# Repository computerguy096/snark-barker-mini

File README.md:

# The Snark Barker Mini - a miniaturized SB 1.0 Clone

The Snark Barker Mini is a function compatible clone of the original [Snark Barker](https://github.com/schlae/snark-barker), made by schlae. It implements all the features of the original Sound Blaster:

- OPL2 FM synth
- digital sound playback and recording
- gameport with MIDI IN/OUT
- SAA1099 (Creative Music System) synth 

The only major difference is the lack of a volume potentiometer. Due to the card's size and parts availability contraints, the volume is pre-set at max output, but this should not be a problem for speaker systems which have adjustable volume.

## Bill Of Materials
An interactive HTML BOM is provided in `/kicad/bom` for easy parts installation. Most passives do not have silkscreen labels so this will be needed. Additionally, a CSV BOM is provided as well.

## The Firmware
This card uses an Atmel 89LP51 as a modern day replacement for the original 80C51 microcontroller Creative used to implement the DSP chip. There is a programming header provided for the DSP chip, which can be flashed with [this HEX file](firmware/sb.hex) using the tool of your choice. 

The DSP PWR jumper needs to be installed for normal operation, and removed when programming the DSP (it connects the DSP to VCC).

## Testing and Diagnostics
The card can be tested using schlae's [SBDIAG](utility/SBDIAG.EXE)

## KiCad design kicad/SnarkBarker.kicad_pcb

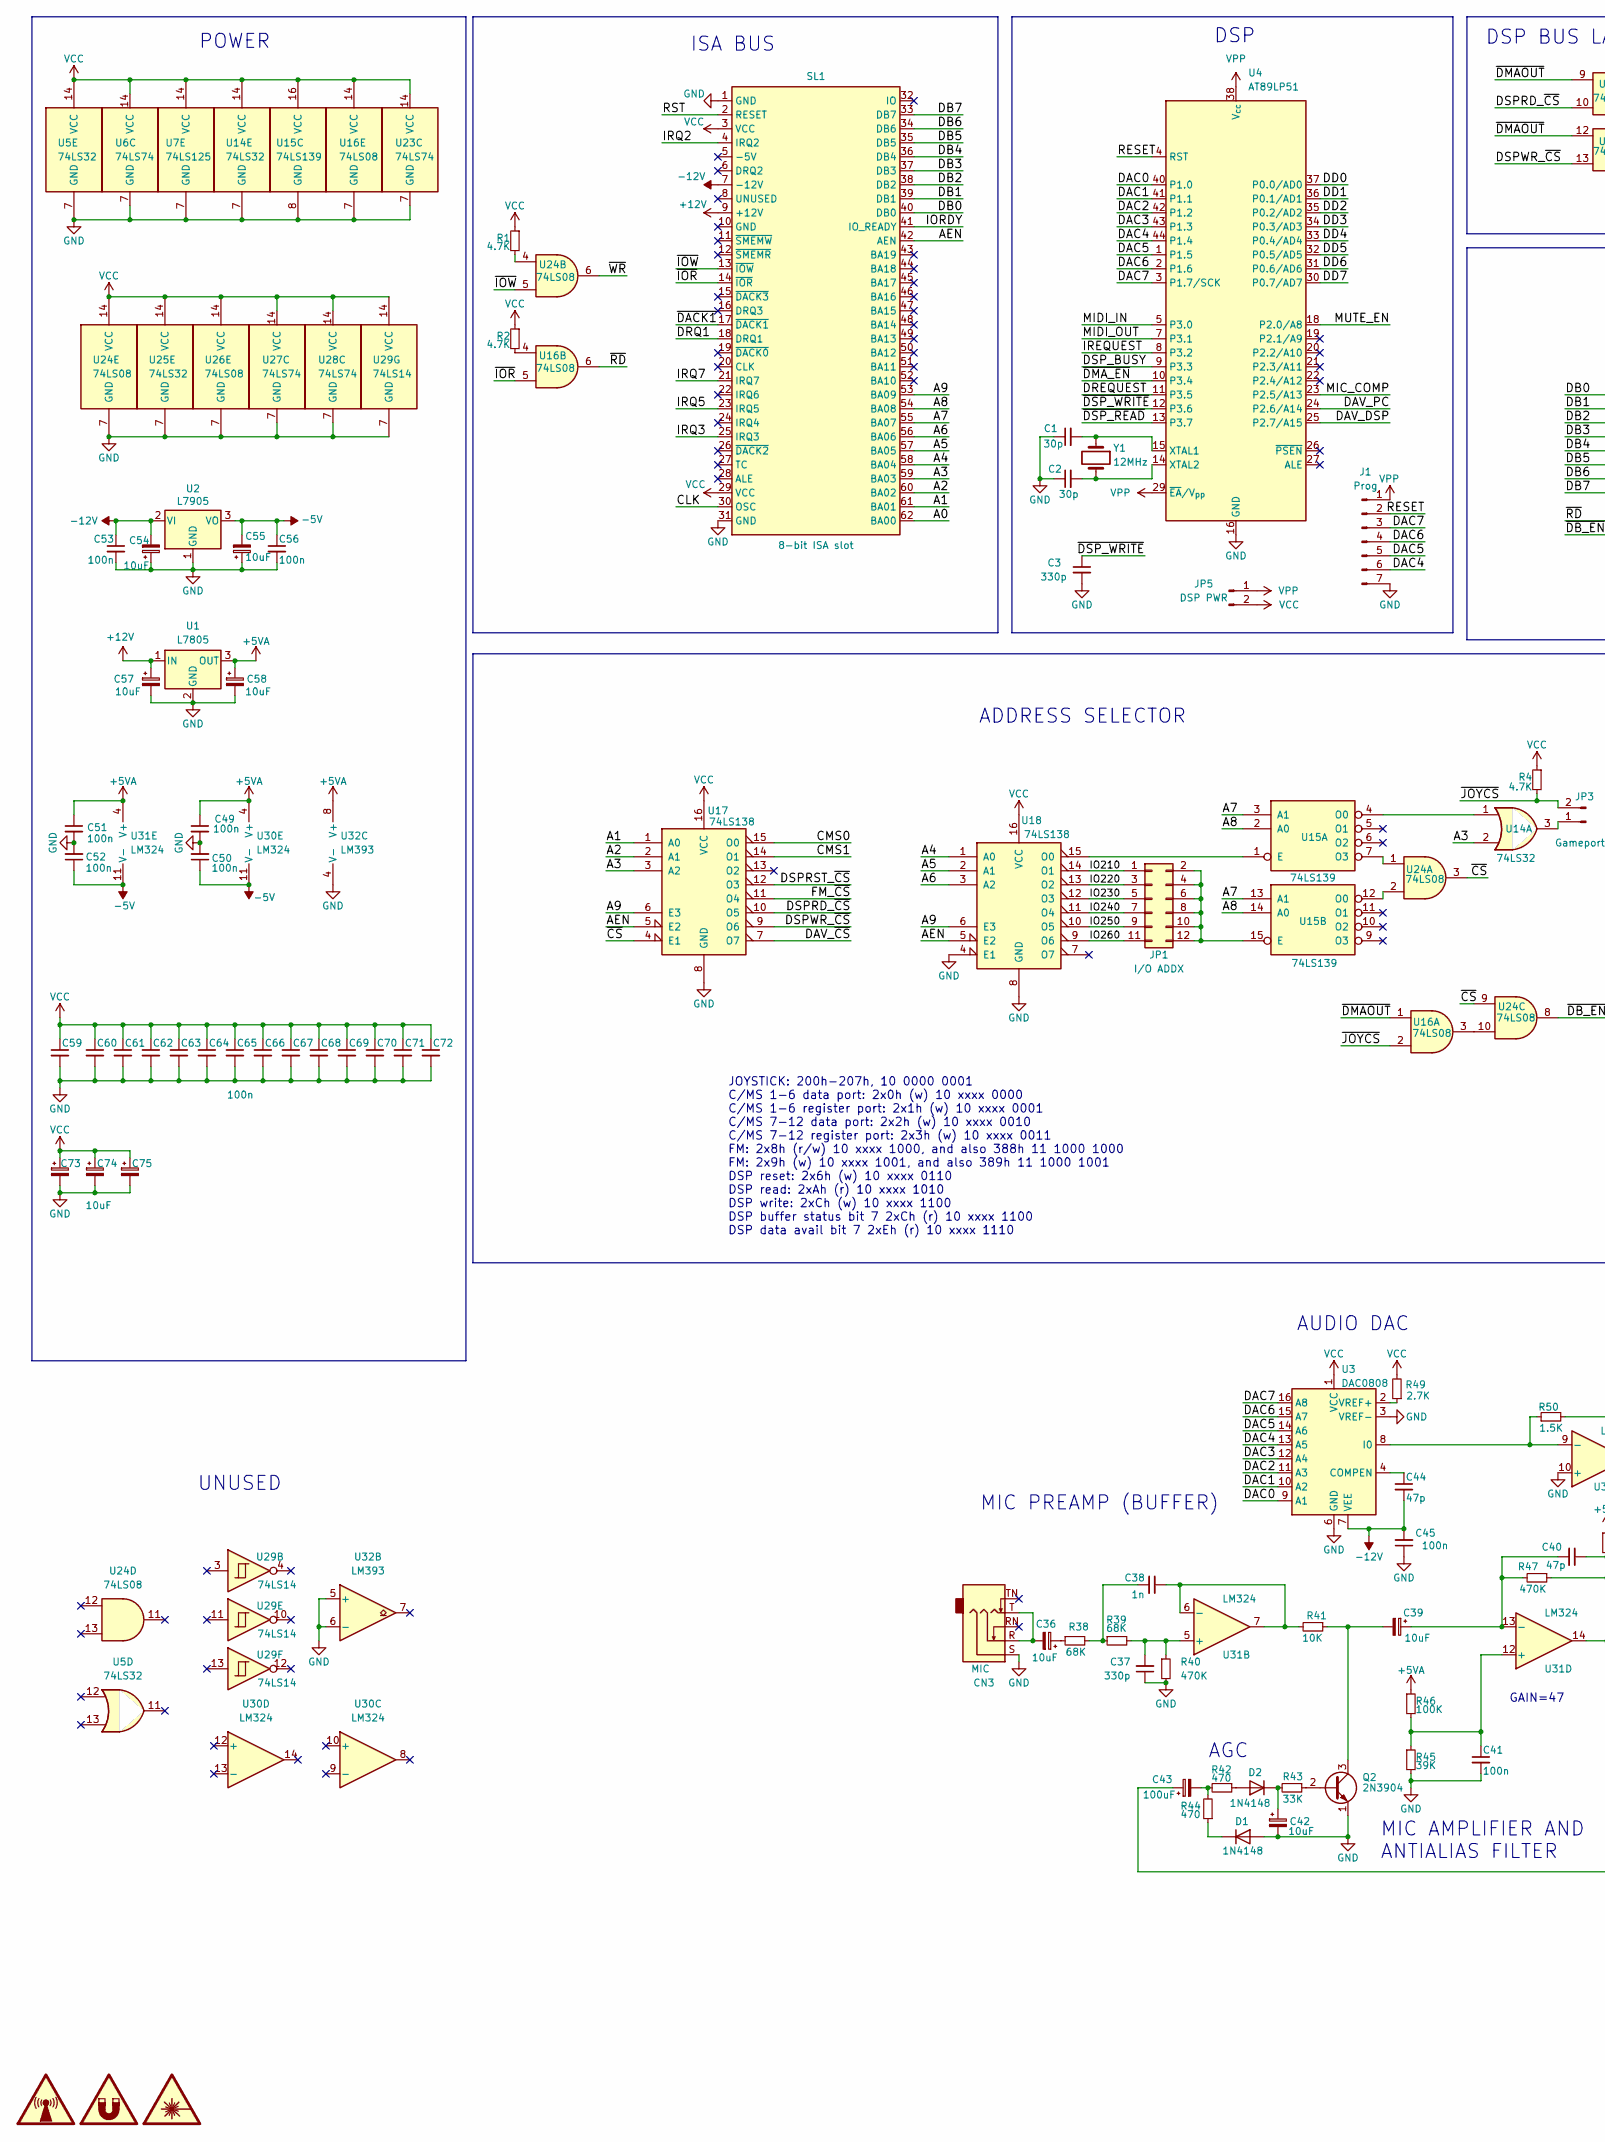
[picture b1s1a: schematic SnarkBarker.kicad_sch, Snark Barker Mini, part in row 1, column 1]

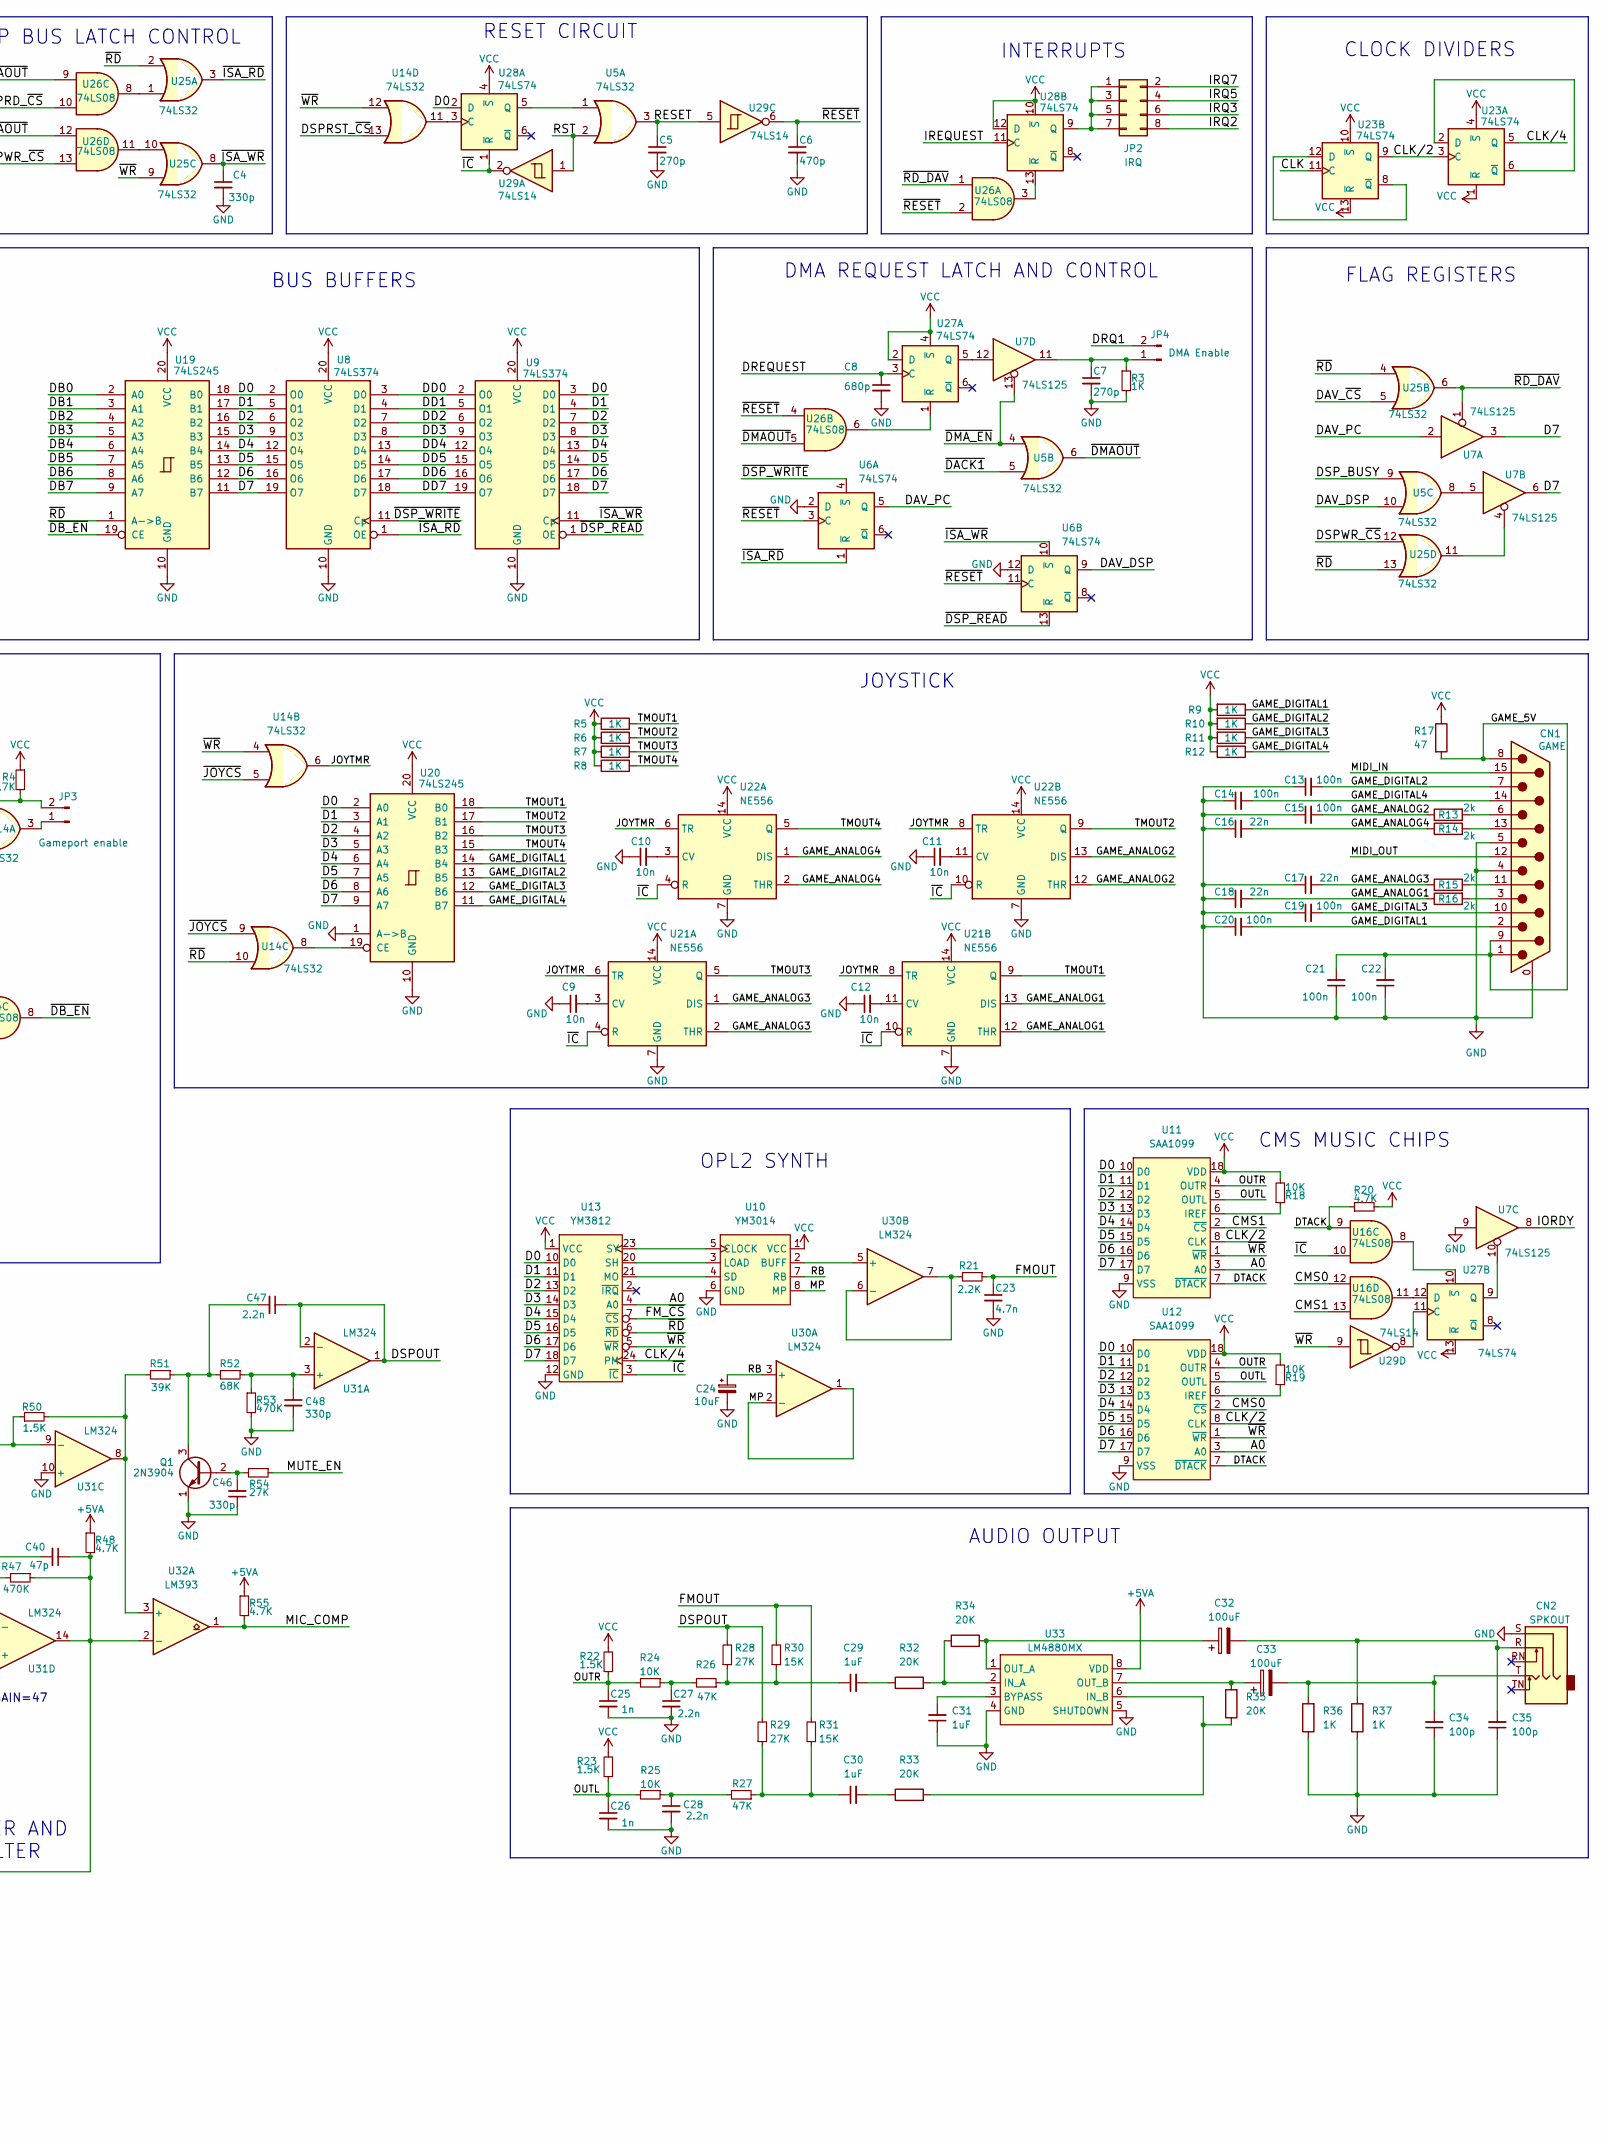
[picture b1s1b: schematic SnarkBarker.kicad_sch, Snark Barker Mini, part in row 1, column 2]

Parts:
C1, C2: 30p; C_0805_2012Metric; Mouser 810-FG28C0G1H270JNT6
C3, C4, C37, C46, C48: 330p; C_0805_2012Metric; Mouser 810-FG28C0G1H331JNT6
C5, C7: 270p; C_0805_2012Metric; Mouser 810-FG28C0G1H271JNT0
C6: 470p; C_0805_2012Metric; Mouser 810-FG28C0G1H471JNT6
C8: 680p; C_0805_2012Metric; Mouser 810-FG28C0G1H681JNT6
C9, C10, C11, C12: 10n; C_0805_2012Metric; Mouser 810-FG28X7R1H103KNT0
C13, C14, C15, C19, C20, C21, C22: 100n; C_0805_2012Metric
C16, C17, C18: 22n; C_0805_2012Metric
C23: 4.7n; C_0805_2012Metric; Mouser 810-FG28C0G1H472JNT6
C24, C36, C39, C42, C54, C55, C57, C58, C73, C74, C75: 10uF; C_1210_3225Metric; Mouser 667-ECA-1CM100I
C25, C26, C38: 1n; C_0805_2012Metric; Mouser 810-FG28X7R1H102KNT6
C27, C28, C47: 2.2n; C_0805_2012Metric; Mouser 810-FG28X7R1H222KNT6
C29, C30, C31: 1uF; C_0805_2012Metric
C32, C33: 100uF; CP_Elec_6.3x5.2
C34, C35: 100p; C_0805_2012Metric
C40, C44: 47p; C_0805_2012Metric; Mouser 810-FG28C0G1H470JNT6
C41, C45, C49, C50, C51, C52, C53, C56, C59, C60, C61, C62, C63, C64, C65, C66, C67, C68, C69, C70, C71, C72: 100n; C_0805_2012Metric; Mouser 581-SA105E104M
C43: 100uF; CP_Elec_6.3x5.2; Mouser 667-ECA-1CM101I
CN1: GAME; DSUB-15_Pins_Horizontal_P2.77x2.84mm_EdgePinOffset7.70mm_Ho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
CN2: SPKOUT; TRS jack
CN3: MIC; TRS jack
D1, D2: 1N4148; D_0805_2012Metric; Mouser 512-1N4148
J1: Prog; PinHeader_1x07_P2.54mm_Vertical
JP1: I/O ADDX; PinHeader_2x06_P2.54mm_Vertical
JP2: IRQ; PinHeader_2x04_P2.54mm_Vertical
JP3: Gameport enable; PinHeader_1x02_P2.54mm_Vertical
JP4: DMA Enable; PinHeader_1x02_P2.54mm_Vertical
JP5: DSP PWR; PinHeader_1x02_P2.54mm_Vertical
Q1, Q2: 2N3904; SOT-23; Mouser 833-2N3904-AP
R1, R2, R4, R20, R48, R55: 4.7K; R_0805_2012Metric; Mouser 603-CFR-25JB-52-4K7
R3: 1K; R_0805_2012Metric; Mouser 603-CFR-25JR-521K
R5, R6, R7, R8, R9, R10, R11, R12, R36, R37: 1K; R_0805_2012Metric
R13, R14, R15, R16: 2k; R_0805_2012Metric
R17: 47; R_0805_2012Metric
R18, R19, R24, R25, R41: 10K; R_0805_2012Metric; Mouser 603-CFR-25JB-52-10K
R21: 2.2K; R_0805_2012Metric; Mouser 603-CFR-25JB-52-2K2
R22, R23: 1.5K; R_0805_2012Metric; Mouser 603-CFR-25JB-52-1K5
R26, R27: 47K; R_0805_2012Metric; Mouser 603-CFR-25JB-52-47K
R28, R29, R54: 27K; R_0805_2012Metric; Mouser 603-CFR-25JB-52-27K
R30, R31: 15K; R_0805_2012Metric; Mouser 603-CFR-25JB-52-15K
R32, R33, R34, R35: 20K; R_0805_2012Metric
R38, R39, R52: 68K; R_0805_2012Metric; Mouser 603-CFR-25JB-52-68K
R40, R47, R53: 470K; R_0805_2012Metric; Mouser 603-CFR-25JR-52470K
R42, R44: 470; R_0805_2012Metric; Mouser 603-CFR-25JB-52-470R
R43: 33K; R_0805_2012Metric; Mouser 603-CFR-25JB-52-33K
R45: 39K; R_0805_2012Metric; Mouser 603-MFR-25FBF52-39K
R46: 100K; R_0805_2012Metric; Mouser 603-MFR-25FBF52-100K
R49: 2.7K; R_0805_2012Metric; Mouser 603-MFR-25FBF52-2K7
R50: 1.5K; R_0805_2012Metric; Mouser 603-MFR-25FBF52-1K5
R51: 39K; R_0805_2012Metric; Mouser 603-CFR-25JB-52-39K
SL1: 8-bit ISA slot; ISA card edge
U1: L7805; TO-220-3_Horizontal_TabDown
U2: L7905; TO-220-3_Horizontal_TabDown
U3: DAC0808; SOIC-16_3.9x9.9mm_P1.27mm
U4: AT89LP51; TQFP-44_10x10mm_P0.8mm
U5, U14: 74LS32; SOIC-14_3.9x8.7mm_P1.27mm
U6: 74LS74; SOIC-14_3.9x8.7mm_P1.27mm
U7: 74LS125; SOIC-14_3.9x8.7mm_P1.27mm; Mouser 595-SN74LS125AN
U8, U9: 74LS374; SOIC-20W_7.5x12.8mm_P1.27mm; Mouser 595-SN74LS374N
U10: YM3014; DIP-8_W7.62mm
U11, U12: SAA1099; DIP-18_W7.62mm
U13: YM3812; DIP-24_W15.24mm
U15: 74LS139; SOIC-16_3.9x9.9mm_P1.27mm; Mouser 595-SN74LS139AN
U16, U24, U26: 74LS08; SOIC-14_3.9x8.7mm_P1.27mm
U17, U18: 74LS138; SOIC-16_3.9x9.9mm_P1.27mm; Mouser 595-SN74LS138NE4
U19, U20: 74LS245; SOIC-20W_7.5x12.8mm_P1.27mm; Mouser 595-SN74LS245N
U21, U22: NE556; SOIC-14_3.9x8.7mm_P1.27mm
U23, U27, U28: 74LS74; SOIC-14_3.9x8.7mm_P1.27mm; Mouser 595-SN74LS74AN
U25: 74LS32; SOIC-14_3.9x8.7mm_P1.27mm; Mouser 595-SN74LS32N
U29: 74LS14; SOIC-14_3.9x8.7mm_P1.27mm; Mouser 595-SN74LS14N
U30: LM324; SOIC-14_3.9x8.7mm_P1.27mm
U31: LM324; SOIC-14_3.9x8.7mm_P1.27mm; Mouser 512-LM324AN
U32: LM393; SOIC-8_3.9x4.9mm_P1.27mm
U33: LM4880MX; SO-8_3.9x4.9mm_P1.27mm
Y1: 12MHz; Crystal_HC49-U_Vertical

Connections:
+5VA: C49.1, C51.1, C58.1, R46.1, R48.1, R55.1, U1.3 (OUT), U30.4 (V+), U31.4 (V+), U32.8 (V+), U33.8 (VDD)
+12V: C57.1, SL1.9 (+12V), U1.1 (IN)
-5V: C50.1, C52.1, C55.2, C56.1, U2.3 (VO), U30.11 (V-), U31.11 (V-)
-12V: C44.2, C45.2, C53.1, C54.2, SL1.7 (-12V), U2.2 (VI), U3.7 (VEE)
/A0: SL1.62 (BA00), U11.3 (A0), U12.3 (A0), U13.4 (A0)
/A1: SL1.61 (BA01), U17.1 (A0)
/A2: SL1.60 (BA02), U17.2 (A1)
/A3: SL1.59 (BA03), U14.2, U17.3 (A2)
/A4: SL1.58 (BA04), U18.1 (A0)
/A5: SL1.57 (BA05), U18.2 (A1)
/A6: SL1.56 (BA06), U18.3 (A2)
/A7: SL1.55 (BA07), U15.3 (A1), U15.13 (A1)
/A8: SL1.54 (BA08), U15.2 (A0), U15.14 (A0)
/A9: SL1.53 (BA09), U17.6 (E3), U18.6 (E3)
/AEN: SL1.42 (AEN), U17.5 (E2), U18.5 (E2)
/CLK: SL1.30 (OSC), U23.11 (C)
/CLK/2: U11.8 (CLK), U12.8 (CLK), U23.3 (C), U23.9 (Q)
/CLK/4: U13.24 (PM), U23.5 (Q)
/CMS0: U12.2 (~CS), U16.12, U17.15 (O0)
/CMS1: U11.2 (~CS), U16.13, U17.14 (O1)
/D0: U8.2 (O0), U9.3 (D0), U11.10 (D0), U12.10 (D0), U13.10 (D0), U19.18 (B0), U20.2 (A0), U28.2 (D)
/D1: U8.5 (O1), U9.4 (D1), U11.11 (D1), U12.11 (D1), U13.11 (D1), U19.17 (B1), U20.3 (A1)
/D2: U8.6 (O2), U9.7 (D2), U11.12 (D2), U12.12 (D2), U13.13 (D2), U19.16 (B2), U20.4 (A2)
/D3: U8.9 (O3), U9.8 (D3), U11.13 (D3), U12.13 (D3), U13.14 (D3), U19.15 (B3), U20.5 (A3)
/D4: U8.12 (O4), U9.13 (D4), U11.14 (D4), U12.14 (D4), U13.15 (D4), U19.14 (B4), U20.6 (A4)
/D5: U8.15 (O5), U9.14 (D5), U11.15 (D5), U12.15 (D5), U13.16 (D5), U19.13 (B5), U20.7 (A5)
/D6: U8.16 (O6), U9.17 (D6), U11.16 (D6), U12.16 (D6), U13.17 (D6), U19.12 (B6), U20.8 (A6)
/D7: U7.3, U7.6, U8.19 (O7), U9.18 (D7), U11.17 (D7), U12.17 (D7), U13.18 (D7), U19.11 (B7), U20.9 (A7)
/DAC0: U3.9 (A1), U4.40 (P1.0)
/DAC1: U3.10 (A2), U4.41 (P1.1)
/DAC2: U3.11 (A3), U4.42 (P1.2)
/DAC3: U3.12 (A4), U4.43 (P1.3)
/DAC4: J1.6, U3.13 (A5), U4.44 (P1.4)
/DAC5: J1.5, U3.14 (A6), U4.1 (P1.5)
/DAC6: J1.4, U3.15 (A7), U4.2 (P1.6)
/DAC7: J1.3, U3.16 (A8), U4.3 (P1.7/SCK)
/DAV_DSP: U4.25 (P2.7/A15), U5.10, U6.9 (Q)
/DAV_PC: U4.24 (P2.6/A14), U6.5 (Q), U7.2
/DAV_~CS: U17.7 (O7), U25.5
/DB0: SL1.40 (DB0), U19.2 (A0)
/DB1: SL1.39 (DB1), U19.3 (A1)
/DB2: SL1.38 (DB2), U19.4 (A2)
/DB3: SL1.37 (DB3), U19.5 (A3)
/DB4: SL1.36 (DB4), U19.6 (A4)
/DB5: SL1.35 (DB5), U19.7 (A5)
/DB6: SL1.34 (DB6), U19.8 (A6)
/DB7: SL1.33 (DB7), U19.9 (A7)
/DD0: U4.37 (P0.0/AD0), U8.3 (D0), U9.2 (O0)
/DD1: U4.36 (P0.1/AD1), U8.4 (D1), U9.5 (O1)
/DD2: U4.35 (P0.2/AD2), U8.7 (D2), U9.6 (O2)
/DD3: U4.34 (P0.3/AD3), U8.8 (D3), U9.9 (O3)
/DD4: U4.33 (P0.4/AD4), U8.13 (D4), U9.12 (O4)
/DD5: U4.32 (P0.5/AD5), U8.14 (D5), U9.15 (O5)
/DD6: U4.31 (P0.6/AD6), U8.17 (D6), U9.16 (O6)
/DD7: U4.30 (P0.7/AD7), U8.18 (D7), U9.19 (O7)
/DREQUEST: C8.1, U4.11 (P3.5), U27.3 (C)
/DRQ1: JP4.2, SL1.18 (DRQ1)
/DSPOUT: C47.1, R28.2, R29.2, U31.1, U31.2 (-)
/DSPRD_~CS: U17.10 (O5), U26.10
/DSPRST_~CS: U14.13, U17.12 (O3)
/DSPWR_~CS: U17.9 (O6), U25.12, U26.13
/DSP_BUSY: U4.9 (P3.3), U5.9
/DTACK: R20.1, U11.7 (~DTACK), U12.7 (~DTACK), U16.9
/FMOUT: C23.1, R21.1, R30.2, R31.2
/FM_~CS: U13.7 (~CS), U17.11 (O4)
/GAME_5V: C21.2, C22.2, CN1.1, CN1.8, CN1.9, R17.2
/GAME_ANALOG1: C18.2, R16.1, U21.12 (THR), U21.13 (DIS)
/GAME_ANALOG2: C15.2, R13.1, U22.12 (THR), U22.13 (DIS)
/GAME_ANALOG3: C17.2, R15.1, U21.1 (DIS), U21.2 (THR)
/GAME_ANALOG4: C16.2, R14.1, U22.1 (DIS), U22.2 (THR)
/GAME_DIGITAL1: C20.2, CN1.2, R9.1, U20.14 (B4)
/GAME_DIGITAL2: C13.2, CN1.7, R10.1, U20.13 (B5)
/GAME_DIGITAL3: C19.2, CN1.10, R11.1, U20.12 (B6)
/GAME_DIGITAL4: C14.2, CN1.14, R12.1, U20.11 (B7)
/IO210: JP1.1, U18.14 (O1)
/IO220: JP1.3, U18.13 (O2)
/IO230: JP1.5, U18.12 (O3)
/IO240: JP1.7, U18.11 (O4)
/IO250: JP1.9, U18.10 (O5)
/IO260: JP1.11, U18.9 (O6)
/IORDY: SL1.41 (IO_READY), U7.8
/IREQUEST: U4.8 (P3.2), U28.11 (C)
/IRQ2: JP2.8, SL1.4 (IRQ2)
/IRQ3: JP2.6, SL1.25 (IRQ3)
/IRQ5: JP2.4, SL1.23 (IRQ5)
/IRQ7: JP2.2, SL1.21 (IRQ7)
/JOYTMR: U14.6, U21.6 (TR), U21.8 (TR), U22.6 (TR), U22.8 (TR)
/MIC_COMP: R55.2, U4.23 (P2.5/A13), U32.1
/MIDI_IN: CN1.15, U4.5 (P3.0)
/MIDI_OUT: CN1.12, U4.7 (P3.1)
/MP: U10.8 (MP), U30.1, U30.2 (-)
/MUTE_EN: R54.1, U4.18 (P2.0/A8)
/OUTL: C26.1, R23.1, R25.2, U11.5 (OUTL), U12.5 (OUTL)
/OUTR: C25.1, R22.1, R24.2, U11.4 (OUTR), U12.4 (OUTR)
/RB: C24.1, U10.7 (RB), U30.3 (+)
/RESET: C5.1, J1.2, U4.4 (RST), U5.3, U29.5
/RST: SL1.2 (RESET), U5.2, U29.1
/TMOUT1: R5.2, U20.18 (B0), U21.9 (Q)
/TMOUT2: R6.2, U20.17 (B1), U22.9 (Q)
/TMOUT3: R7.2, U20.16 (B2), U21.5 (Q)
/TMOUT4: R8.2, U20.15 (B3), U22.5 (Q)
/~CS: U17.4 (E1), U24.3, U24.9
/~DACK1: SL1.17 (~DACK1), U5.5
/~DB_EN: U19.19 (CE), U24.8
/~DMAOUT: U5.6, U16.1, U26.5, U26.9, U26.12
/~DMA_EN: U4.10 (P3.4), U5.4, U7.13
/~DSP_READ: U4.13 (P3.7), U6.13 (~R), U9.1 (OE)
/~DSP_WRITE: C3.1, U4.12 (P3.6), U6.4 (~S), U8.11 (Cp)
/~IC: U13.3 (~IC), U16.10, U21.4 (R), U21.10 (R), U22.4 (R), U22.10 (R), U28.1 (~R), U29.2
/~IOR: SL1.14 (~IOR), U16.5
/~IOW: SL1.13 (~IOW), U24.5
/~ISA_RD: U6.1 (~R), U8.1 (OE), U25.3
/~ISA_WR: C4.1, U6.10 (~S), U9.11 (Cp), U25.8
/~JOYCS: JP3.2, R4.2, U14.5, U14.9, U16.2
/~RD_DAV: U7.1, U25.6, U26.1
/~RD: U13.6 (~RD), U14.10, U16.6, U19.1 (A->B), U25.2, U25.4, U25.13
/~RESET: C6.1, U6.3 (C), U6.11 (C), U26.2, U26.4, U29.6
/~WR: U11.1 (~WR), U12.1 (~WR), U13.5 (~WR), U14.4, U14.12, U24.6, U25.9, U29.9
GND: C1.1, C2.1, C3.2, C4.2, C5.2, C6.2, C7.2, C8.2, C9.1, C10.1, C11.1, C12.1, C13.1, C14.1, C15.1, C16.1, C17.1, C18.1, C19.1, C20.1, C21.1, C22.1, C23.2, C24.2, C25.2, C26.2, C27.2, C28.2, C31.1, C34.1, C35.1, C37.1, C41.2, C42.2, C45.1, C46.1, C48.2, C49.2, C50.2, C51.2, C52.2, C53.2, C54.1, C55.1, C56.2, C57.2, C58.2, C59.2, C60.2, C61.2, C62.2, C63.2, C64.2, C65.2, C66.2, C67.2, C68.2, C69.2, C70.2, C71.2, C72.2, C73.2, C74.2, C75.2, CN1.0 (PAD), CN1.4, CN1.5, CN2.S, CN3.S, D1.2 (A), J1.7, Q1.1 (E), Q2.1 (E), R3.2, R36.1, R37.1, R40.2, R45.2, R53.2, SL1.1 (GND), SL1.31 (GND), U1.2 (GND), U2.1 (GND), U3.3 (VREF-), U3.6 (GND), U4.16 (GND), U4.17 (GND), U5.7 (GND), U6.2 (D), U6.7 (GND), U6.12 (D), U7.7 (GND), U7.9, U8.10 (GND), U9.10 (GND), U10.6 (GND), U11.9 (VSS), U12.9 (VSS), U13.12 (GND), U14.7 (GND), U15.8 (GND), U16.7 (GND), U17.8 (GND), U18.4 (E1), U18.8 (GND), U19.10 (GND), U20.1 (A->B), U20.10 (GND), U21.7 (GND), U22.7 (GND), U23.7 (GND), U24.7 (GND), U25.7 (GND), U26.7 (GND), U27.7 (GND), U28.7 (GND), U29.7 (GND), U31.10 (+), U32.4 (V-), U32.5 (+), U32.6 (-), U33.4 (GND), U33.5 (SHUTDOWN)
unnamed: C27.1, R24.1, R26.2
unnamed: C28.1, R25.1, R27.2
unnamed: C29.1, R26.1, R28.1, R30.1
unnamed: C29.2, R32.1
unnamed: C30.1, R27.1, R29.1, R31.1
unnamed: C30.2, R33.1
unnamed: C32.2, C35.2, CN2.R, R37.2
unnamed: C33.2, C34.2, CN2.T, R36.2
unnamed: C36.1, R38.1
unnamed: C36.2, CN3.R, CN3.T
unnamed: C38.2, R38.2, R39.1
unnamed: C43.2, R42.2, R44.2
unnamed: CN1.13, R14.2
unnamed: CN1.11 (P111), R15.2
unnamed: CN1.3, R16.2
unnamed: CN1.6, R13.2
unnamed: D1.1 (K), R44.1
unnamed: D2.2 (A), R42.1
unnamed: C42.1, D2.1 (K), R43.2
unnamed: JP1.2, JP1.4, JP1.6, JP1.8, JP1.10, JP1.12, U15.15 (E)
unnamed: JP2.1, JP2.3, JP2.5, JP2.7, U28.9 (Q)
unnamed: JP3.1, U14.3
unnamed: C7.1, JP4.1, R3.1, U7.11
unnamed: C46.2, Q1.2 (B), R54.2
unnamed: C47.2, Q1.3 (C), R51.1, R52.2
unnamed: Q2.2 (B), R43.1
unnamed: C39.2, Q2.3 (C), R41.1
unnamed: R1.2, U24.4
unnamed: R2.2, U16.4
unnamed: C44.1, U3.4 (COMPEN)
unnamed: R50.1, U3.8 (I0), U31.9 (-)
unnamed: R49.1, U3.2 (VREF+)
unnamed: C1.2, U4.15 (XTAL1), Y1.1
unnamed: C2.2, U4.14 (XTAL2), Y1.2
unnamed: U5.8, U7.5
unnamed: U10.2 (BUFF), U30.5 (+)
unnamed: U10.5 (CLOCK), U13.23 (SY)
unnamed: U10.3 (LOAD), U13.20 (SH)
unnamed: U10.4 (SD), U13.21 (MO)
unnamed: R18.1, U11.6 (IREF)
unnamed: R19.1, U12.6 (IREF)
unnamed: U15.1 (E), U18.15 (O0)
unnamed: U14.1, U15.4 (O0)
unnamed: U15.7 (O3), U24.1
unnamed: U15.12 (O0), U24.2
unnamed: U16.3, U24.10
unnamed: U14.8, U20.19 (CE)
unnamed: C9.2, U21.3 (CV)
unnamed: C12.2, U21.11 (CV)
unnamed: C10.2, U22.3 (CV)
unnamed: C11.2, U22.11 (CV)
unnamed: U23.2 (D), U23.6 (~Q)
unnamed: U23.8 (~Q), U23.12 (D)
unnamed: U25.1, U26.8
unnamed: U25.10, U26.11
unnamed: U7.4, U25.11
unnamed: U7.12, U27.5 (Q)
unnamed: U26.6, U27.1 (~R)
unnamed: U27.11 (C), U29.8
unnamed: U16.11, U27.12 (D)
unnamed: U7.10, U27.9 (Q)
unnamed: U16.8, U27.10 (~S)
unnamed: U14.11, U28.3 (C)
unnamed: U5.1, U28.5 (Q)
unnamed: U26.3, U28.13 (~R)
unnamed: R21.2, U30.6 (-), U30.7
unnamed: C48.1, R52.1, R53.1, U31.3 (+)
unnamed: C37.2, R39.2, R40.1, U31.5 (+)
unnamed: C38.1, R41.2, U31.6 (-), U31.7
unnamed: C41.1, R45.1, R46.2, U31.12 (+)
unnamed: C39.1, C40.2, R47.2, U31.13 (-)
unnamed: R50.2, R51.2, U31.8, U32.3 (+)
unnamed: C40.1, C43.1, R47.1, R48.2, U31.14, U32.2 (-)
unnamed: C31.2, U33.3 (BYPASS)
unnamed: R32.2, R34.1, U33.2 (IN_A)
unnamed: R33.2, R35.1, U33.6 (IN_B)
unnamed: C32.1, R34.2, U33.1 (OUT_A)
unnamed: C33.1, R35.2, U33.7 (OUT_B)
VCC: C59.1, C60.1, C61.1, C62.1, C63.1, C64.1, C65.1, C66.1, C67.1, C68.1, C69.1, C70.1, C71.1, C72.1, C73.1, C74.1, C75.1, JP5.2, R1.1, R2.1, R4.1, R5.1, R6.1, R7.1, R8.1, R9.2, R10.2, R11.2, R12.2, R17.1, R18.2, R19.2, R20.2, R22.2, R23.2, R49.2, SL1.3 (VCC), SL1.29 (VCC), U3.1 (VCC), U5.14 (VCC), U6.14 (VCC), U7.14 (VCC), U8.20 (VCC), U9.20 (VCC), U10.1 (VCC), U11.18 (VDD), U12.18 (VDD), U13.1 (VCC), U14.14 (VCC), U15.16 (VCC), U16.14 (VCC), U17.16 (VCC), U18.16 (VCC), U19.20 (VCC), U20.20 (VCC), U21.14 (VCC), U22.14 (VCC), U23.1 (~R), U23.4 (~S), U23.10 (~S), U23.13 (~R), U23.14 (VCC), U24.14 (VCC), U25.14 (VCC), U26.14 (VCC), U27.2 (D), U27.4 (~S), U27.13 (~R), U27.14 (VCC), U28.4 (~S), U28.10 (~S), U28.12 (D), U28.14 (VCC), U29.14 (VCC)
VPP: J1.1, JP5.1, U4.29 (~EA/V_{pp}), U4.38 (V_{cc})

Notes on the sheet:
DSP BUS LATCH CONTROL
POWER
GAIN=47
BUS BUFFERS
AUDIO OUTPUT
OPL2 SYNTH
RESET CIRCUIT
MIC PREAMP (BUFFER)
AGC
CMS MUSIC CHIPS
JOYSTICK
ADDRESS SELECTOR
ISA BUS
JOYSTICK: 200h-207h, 10 0000 0001 C/MS 1-6 data port: 2x0h (w) 10 xxxx 0000 C/MS 1-6 register port: 2x1h (w) 10 xxxx 0001 C/MS 7-12 data port: 2x2h (w) 10 xxxx 0010 C/MS 7-12 register port: 2x3h (w) 10 xxxx 0011 FM: 2x8h (r/w) 10 xxxx 1000, and also 388h 11 1000 1000 FM: 2x9h (w) 10 xxxx 1001, and 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
INTERRUPTS
DMA REQUEST LATCH AND CONTROL
DSP
AUDIO DAC
MIC AMPLIFIER AND ANTIALIAS FILTER
UNUSED
FLAG REGISTERS
CLOCK DIVIDERS

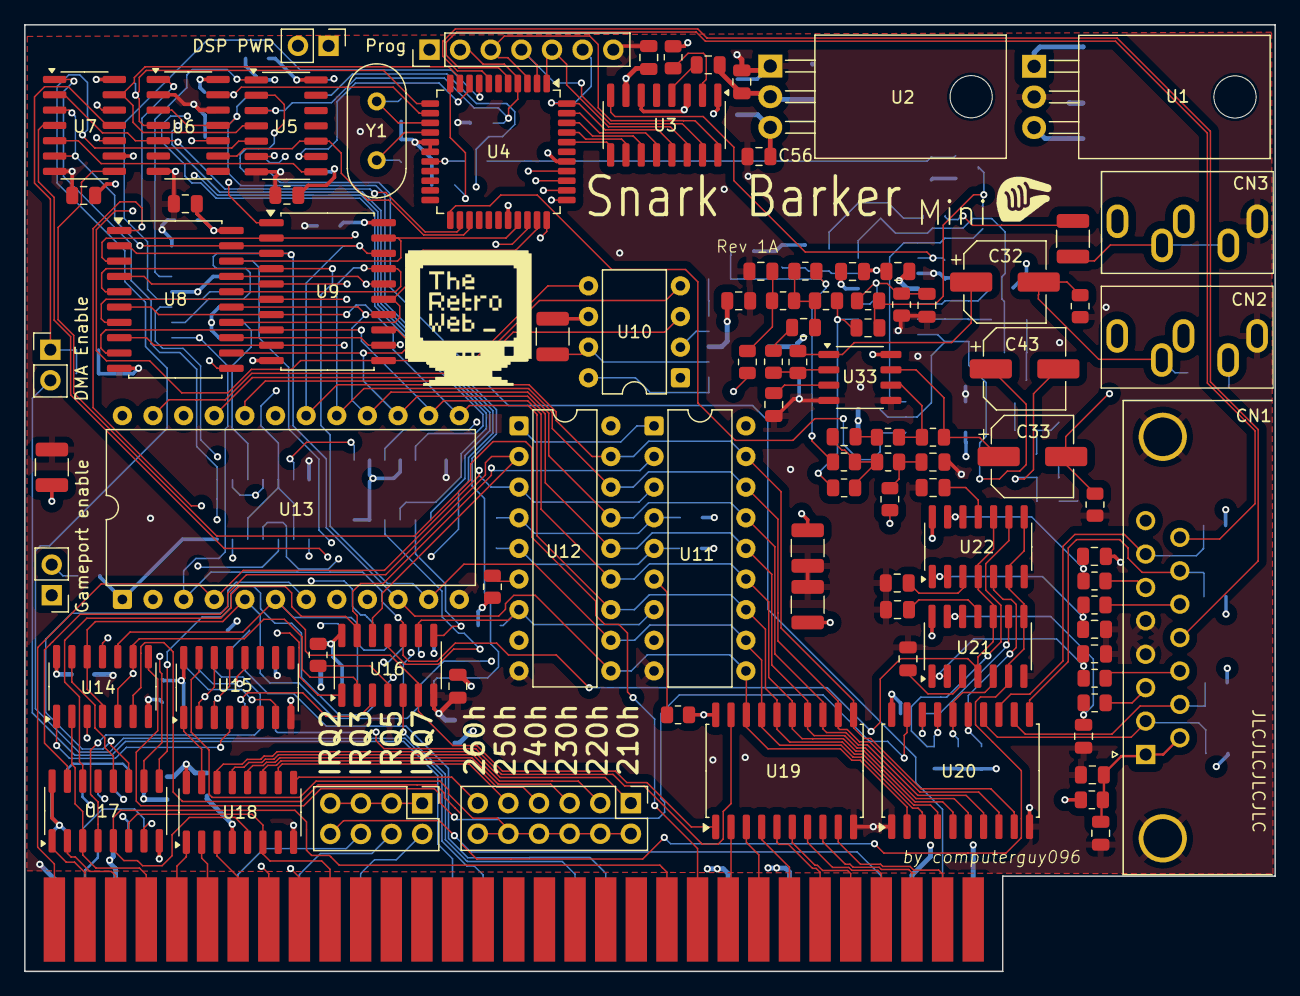
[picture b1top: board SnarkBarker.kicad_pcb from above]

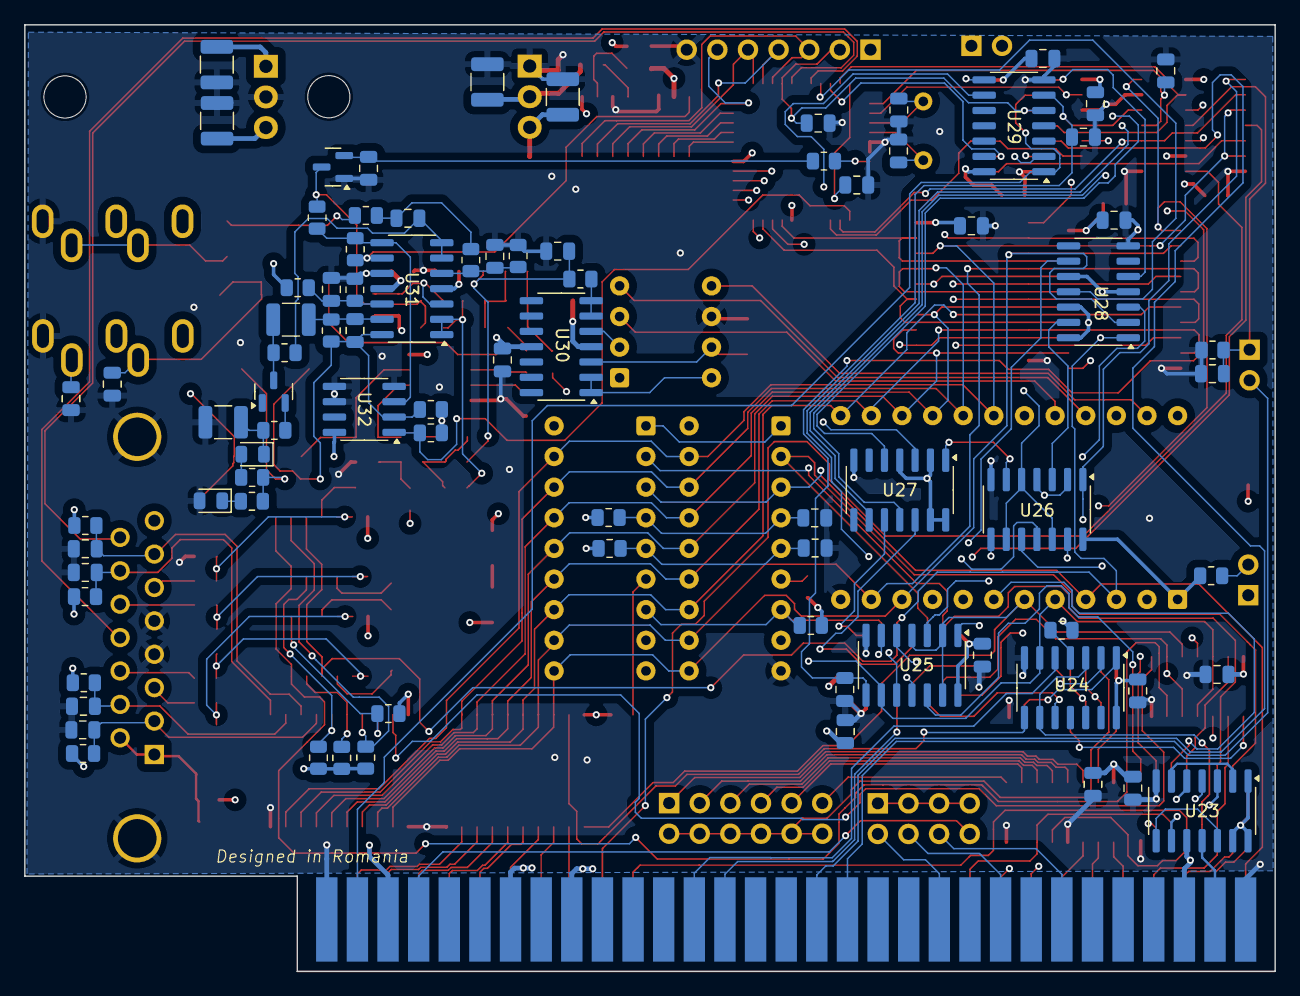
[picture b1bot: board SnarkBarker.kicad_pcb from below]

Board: 4 copper layers, 103.7 x 78.5 mm, 179 parts (83 on the bottom side), 199 nets.

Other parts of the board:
G1: LOGO; trw_logo

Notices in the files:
kicad/SnarkBarker.kicad_pcb:
Copyright (C) 2018 Eric Schlaepfer
License. See https://creativecommons.org/licenses/by-sa/4.0
This work is licensed under a Creative Commons Attribution-ShareAlike 4.0 International
